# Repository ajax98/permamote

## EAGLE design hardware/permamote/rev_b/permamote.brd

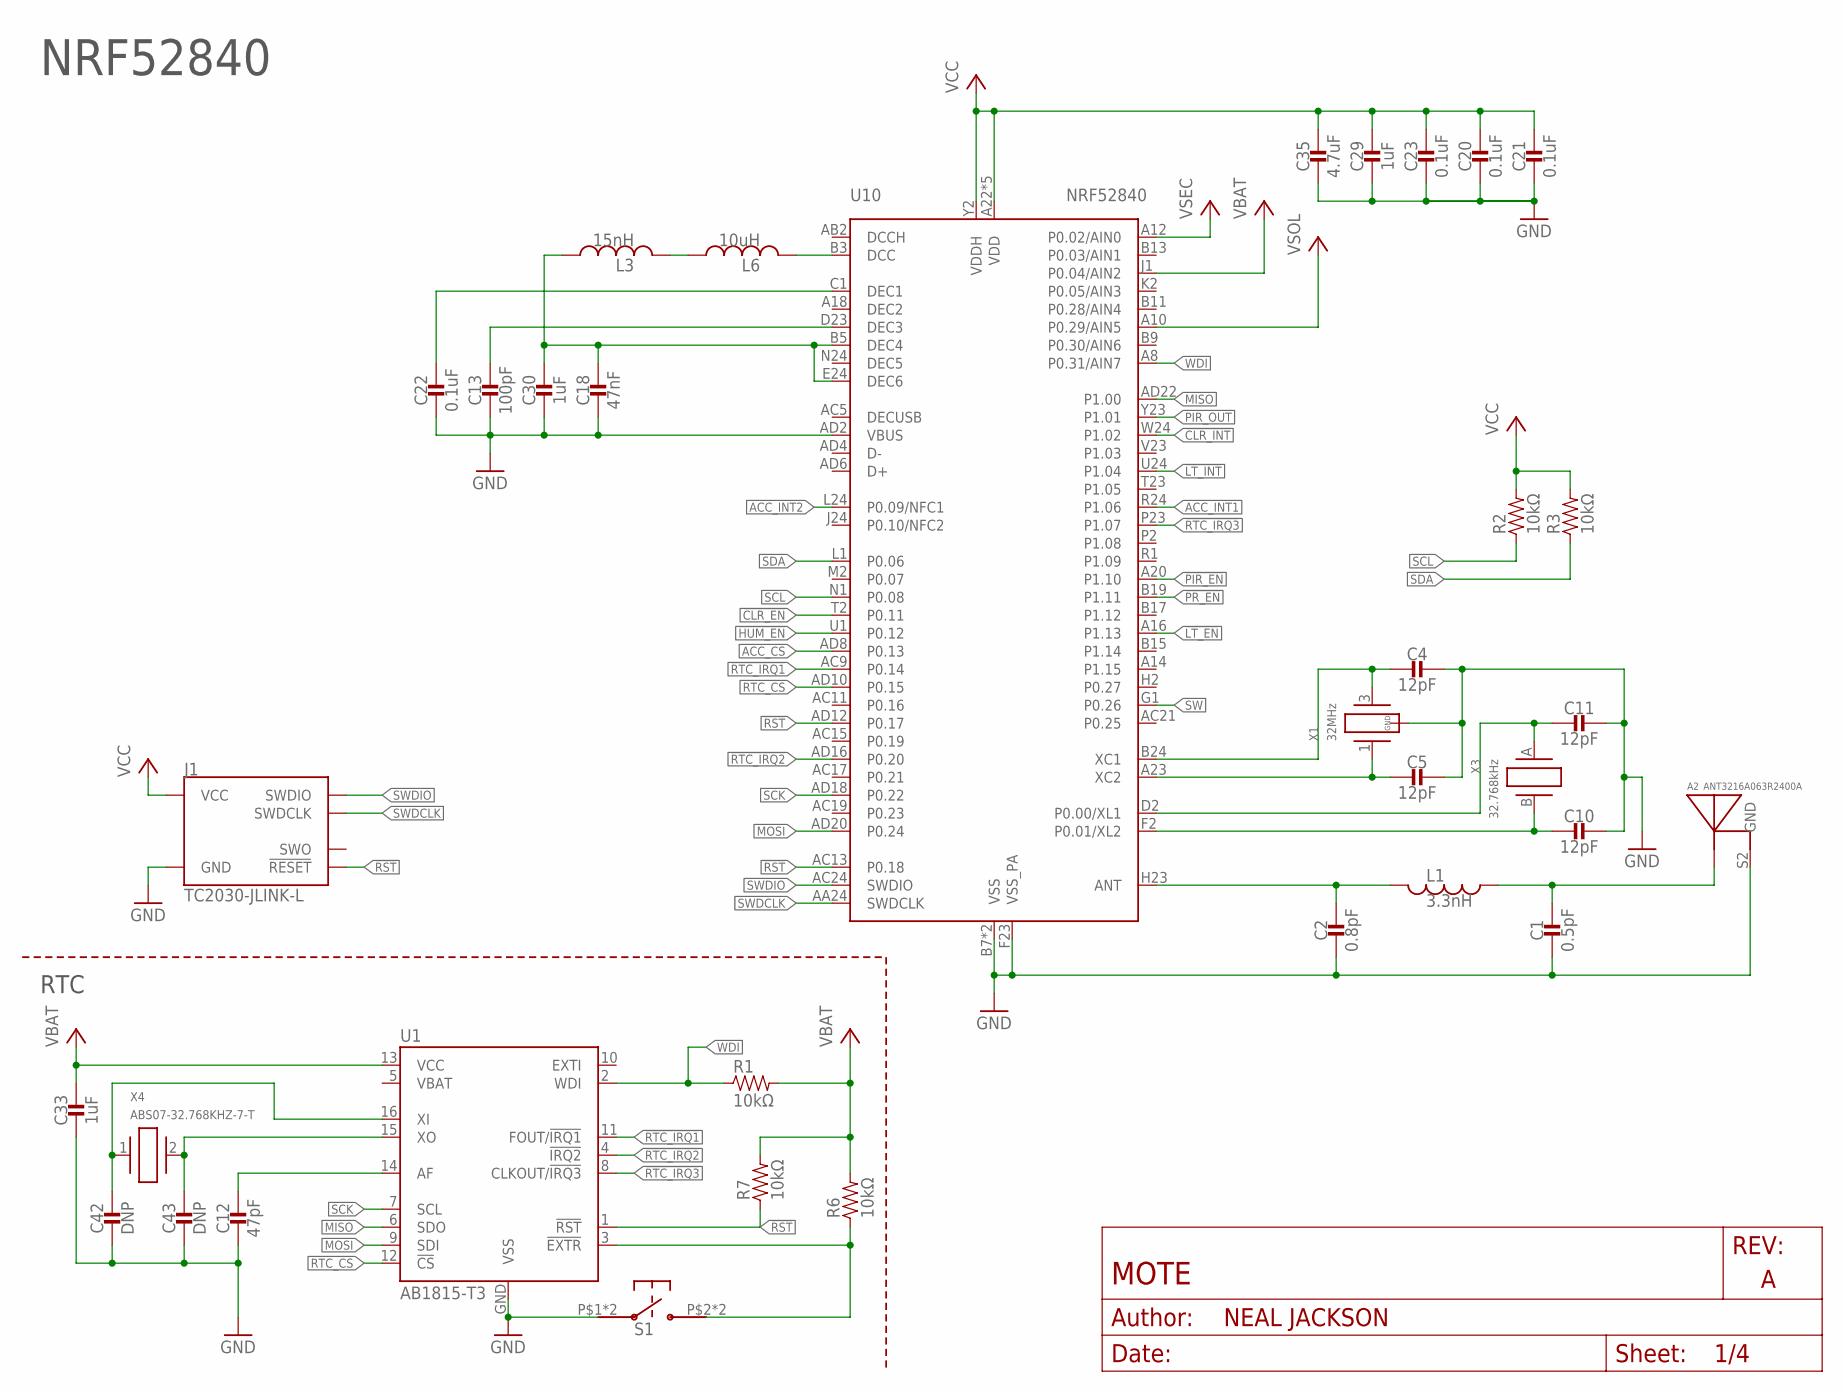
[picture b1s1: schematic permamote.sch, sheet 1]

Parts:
A2: ANT3216A063R2400A
C1: 0.5pF; 0402_CAP; DIGIKEY 490-6264-1-ND
C2: 0.8pF; 0402_CAP; DIGIKEY 490-6269-1-ND
C4, C5, C10, C11: 12pF; 0402_CAP; DIGIKEY 490-6197-1-ND
C12: 47pF; 0402_CAP; DIGIKEY 490-5942-1-ND
C13: 100pF; 0402_CAP; DIGIKEY 490-5922-1-ND
C18: 47nF; 0402_CAP; DIGIKEY 445-1264-1-ND
C20, C21, C22, C23: 0.1uF; 0402_CAP; DIGIKEY 490-6328-1-ND
C29, C30, C33: 1uF; 0402_CAP; DIGIKEY 490-7195-1-ND
C35: 4.7uF; 0402_CAP; DIGIKEY 445-5947-1-ND
C42, C43: DNP; 0402_CAP
J1: TC2030-JLINK-L; TC2030-IDC
L1: 3.3nH; 0402_CAP; DIGIKEY 535-10426-1-ND
L3: 15nH; 0402_CAP; DIGIKEY 587-1521-1-ND
L6: 10uH; 0603_CAP; DIGIKEY 490-4025-1-ND
R1, R2, R3, R6, R7: 10kΩ; 0402_RES; DIGIKEY 311-10KJRCT-ND
S1: EVQP2
U1: AB1815-T3; QFN-16-3MM
U10: NRF52840; AQFN73
X1: 32MHz; TXC-7V
X3: 32.768kHz; ABS05
X4: ABS07-32.768KHZ-7-T; 2-SMD

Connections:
!CLR_EN: U10.T2 (P0.11); also elsewhere on the board
!CLR_INT: U10.W24 (P1.02); also elsewhere on the board
!HUM_EN: U10.U1 (P0.12); also elsewhere on the board
!LT_EN: U10.A16 (P1.13); also elsewhere on the board
!LT_INT: U10.U24 (P1.04); also elsewhere on the board
!PIR_EN: U10.A20 (P1.10); also elsewhere on the board
!PR_EN: U10.B19 (P1.11); also elsewhere on the board
!RST: J1.3 (!RESET), R7.1, U1.1 (!RST), U10.AC13 (P0.18), U10.AD12 (P0.17); also elsewhere on the board
!RTC_EXTR: R6.1, S1.P$2, S1.P$4, U1.3 (!EXTR)
!RTC_IRQ1: U1.11 (FOUT/!IRQ1), U10.AC9 (P0.14); also elsewhere on the board
!RTC_IRQ2: U1.4 (!IRQ2), U10.AD16 (P0.20); also elsewhere on the board
!RTC_IRQ3: U1.8 (CLKOUT/!IRQ3), U10.P23 (P1.07); also elsewhere on the board
ACC_CS: U10.AD8 (P0.13); also elsewhere on the board
ACC_INT1: U10.R24 (P1.06); also elsewhere on the board
ACC_INT2: U10.L24 (P0.09/NFC1); also elsewhere on the board
GND: A2.S2 (GND), C1.2, C2.2, C4.1, C5.1, C10.1, C11.1, C12.2, C13.2, C18.2, C20.2, C21.2, C22.2, C23.2, C29.2, C30.2, C33.2, C35.2, C42.2, C43.2, J1.5 (GND), S1.P$1, S1.P$3, U1.GND (VSS), U10.AD2 (VBUS), U10.B7 (VSS), U10.F23 (VSS_PA), U10.GND (VSS), X1.2 (GND), X1.4 (GND); also elsewhere on the board
MISO: U1.6 (SDO), U10.AD22 (P1.00); also elsewhere on the board
MOSI: U1.9 (SDI), U10.AD20 (P0.24); also elsewhere on the board
unnamed: C22.1, U10.C1 (DEC1)
unnamed: C18.1, C30.1, L3.1, U10.B5 (DEC4), U10.E24 (DEC6)
unnamed: C13.1, U10.D23 (DEC3)
unnamed: C2.1, L1.2, U10.H23 (ANT)
unnamed: A2.S1 (ANTENNA), C1.1, L1.1
unnamed: C4.2, U10.B24 (XC1), X1.3 (2)
unnamed: C5.2, U10.A23 (XC2), X1.1
unnamed: C12.1, U1.14 (AF)
unnamed: C42.1, U1.16 (XI), X4.1
unnamed: C43.1, U1.15 (XO), X4.2
unnamed: L6.2, U10.B3 (DCC)
unnamed: L3.2, L6.1
PIR_OUT: U10.Y23 (P1.01); also elsewhere on the board
RTC_CS: U1.12 (!CS), U10.AD10 (P0.15); also elsewhere on the board
SCK: U1.7 (SCL), U10.AD18 (P0.22); also elsewhere on the board
SCL: R2.1, U10.N1 (P0.08); also elsewhere on the board
SDA: R3.1, U10.L1 (P0.06); also elsewhere on the board
SW: U10.G1 (P0.26); also elsewhere on the board
SWDCLK: J1.4 (SWDCLK), U10.AA24 (SWDCLK)
SWDIO: J1.2 (SWDIO), U10.AC24 (SWDIO)
VBAT: C33.1, R1.2, R6.2, R7.2, U1.13 (VCC), U10.J1 (P0.04/AIN2); also elsewhere on the board
VCC: C20.1, C21.1, C23.1, C29.1, C35.1, J1.1 (VCC), R2.2, R3.2, U10.A22 (VDD), U10.AD14 (VDD), U10.AD23 (VDD), U10.B1 (VDD), U10.W1 (VDD), U10.Y2 (VDDH); also elsewhere on the board
VSEC: U10.A12 (P0.02/AIN0); also elsewhere on the board
VSOL: U10.A10 (P0.29/AIN5); also elsewhere on the board
WDI: R1.1, U1.2 (WDI), U10.A8 (P0.31/AIN7); also elsewhere on the board
XL1: C11.2, U10.D2 (P0.00/XL1), X3.A (1)
XL2: C10.2, U10.F2 (P0.01/XL2), X3.B (2)

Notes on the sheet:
NRF52840
RTC

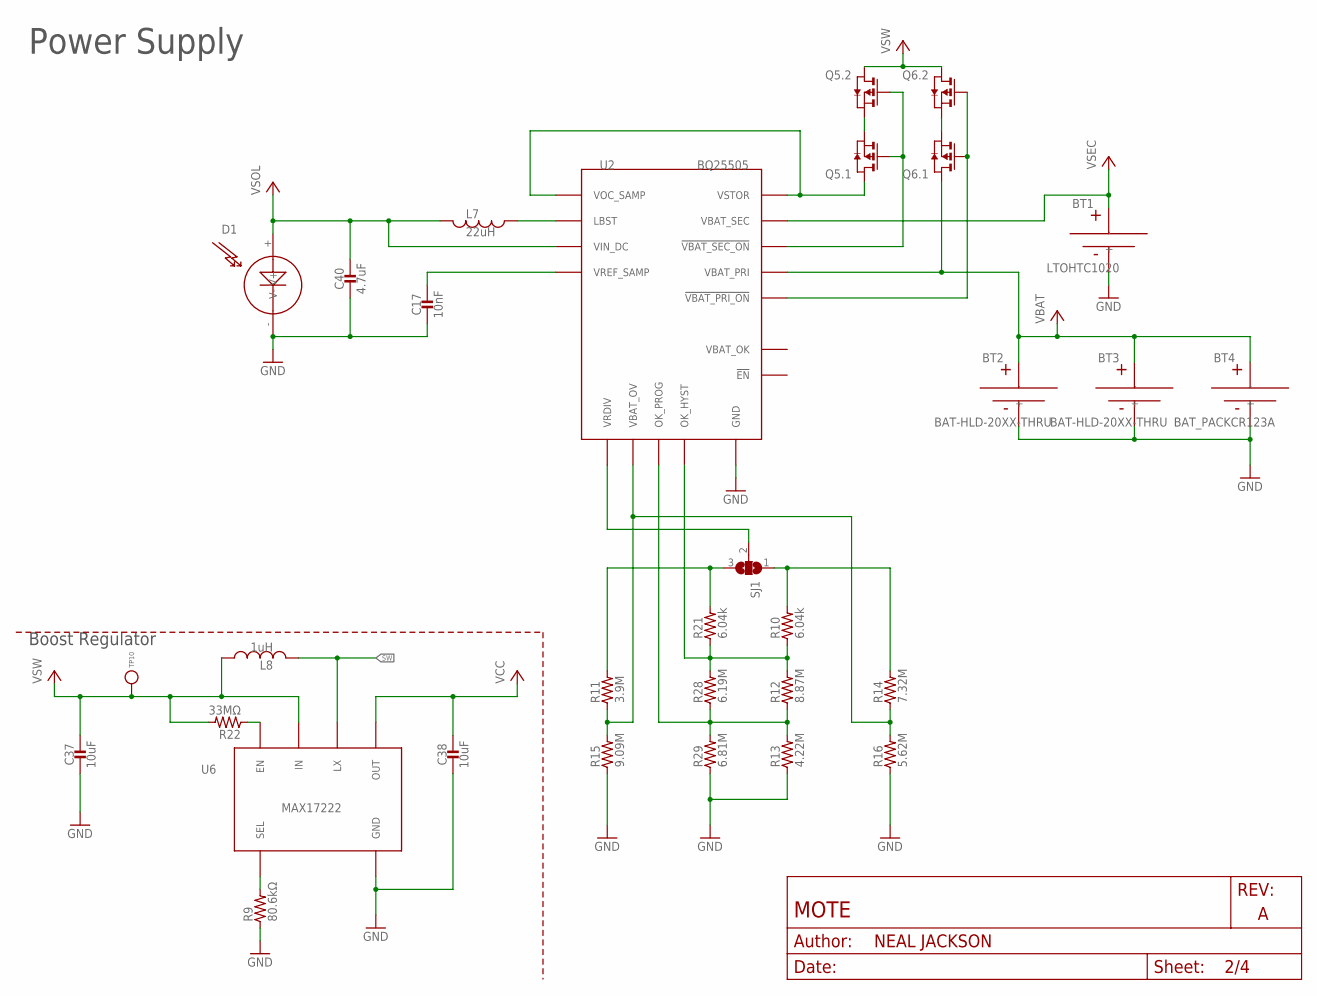
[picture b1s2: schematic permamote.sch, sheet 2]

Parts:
BT1: LTOHTC1020; 1020
BT2, BT3: BAT-HLD-20XX-THRU
BT4: BAT_PACKCR123A; BH123A
C17: 10nF; 0603_CAP; DIGIKEY 490-4516-1-ND
C37, C38: 10uF; 0603_CAP; DIGIKEY 490-3896-1-ND
C40: 4.7uF; 0603_CAP; DIGIKEY 490-3896-1-ND
D1: SOLARCELL; SOLAR_HOLES
L7: 22uH; 74437324220; DIGIKEY 732-3340-1-ND
L8: 1uH; IHL-1212BZ-11; MPN IHLP1212BZER1R0M11; DIGIKEY 541-1319-1-ND
Q5, Q6: PMDXB950UPEL; XDFN-6
R9: 80.6kΩ; 0603-RES; DIGIKEY 311-80.6KHRCT-ND
R10, R21: 6.04k; 0402_RES; DIGIKEY YAG3306CT-ND
R11: 3.9M; 0402_RES; DIGIKEY YAG3306CT-ND
R12: 8.87M; 0402_RES; DIGIKEY YAG3306CT-ND
R13: 4.22M; 0402_RES; DIGIKEY YAG3306CT-ND
R14: 7.32M; 0402_RES; DIGIKEY YAG3306CT-ND
R15: 9.09M; 0402_RES; DIGIKEY YAG3306CT-ND
R16: 5.62M; 0402_RES; DIGIKEY YAG3306CT-ND
R22: 33MΩ; 0603-RES; DIGIKEY HMC0603JT33M0CT-ND
R28: 6.19M; 0402_RES; DIGIKEY YAG3306CT-ND
R29: 6.81M; 0402_RES; DIGIKEY YAG3306CT-ND
SJ1: SJ2W; SJ_2
TP10: TEST_POINT_0.040IN; TESTPOINT_0.040IN
U2: BQ25505; S-PVQFN-N20-RGR
U6: MAX17222; UDFN-6-MAXIM

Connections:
GND: BT1.-, BT2.GND (-), BT3.GND (-), BT4.-, C17.2, C37.2, C38.2, C40.2, D1.- (V-), R9.1, R13.1, R15.1, R16.1, R29.1, U2.1 (GND), U2.6 (GND), U2.15 (GND), U2.16 (GND), U2.17 (GND), U2.PAD (GND), U6.3 (GND); also elsewhere on the board
unnamed: R11.2, R21.2, SJ1.3
unnamed: R9.2, U6.4 (SEL)
unnamed: R22.1, U6.6 (EN)
unnamed: R10.2, R14.2, SJ1.1
unnamed: R11.1, R14.1, R15.2, R16.2, U2.7 (VBAT_OV)
unnamed: C17.1, U2.4 (VREF_SAMP)
unnamed: SJ1.2, U2.8 (VRDIV)
unnamed: L7.P$1 (1), U2.20 (LBST)
unnamed: Q5.1 (S), Q5.4 (S)
unnamed: Q5.2 (G), Q5.5 (G), U2.9 (!VBAT_SEC_ON)
unnamed: Q5.6 (D), U2.3 (VOC_SAMP), U2.19 (VSTOR)
unnamed: Q6.1 (S), Q6.4 (S)
unnamed: Q6.2 (G), Q6.5 (G), U2.10 (!VBAT_PRI_ON)
unnamed: R12.1, R13.2, R28.1, R29.2, U2.12 (OK_PROG)
unnamed: R10.1, R12.2, R21.1, R28.2, U2.11 (OK_HYST)
SW: L8.P$2 (2), U6.2 (LX); also elsewhere on the board
VBAT: BT2.+1 (+), BT2.+2 (+), BT2.+3 (+), BT2.+4 (+), BT3.+1 (+), BT3.+2 (+), BT3.+3 (+), BT3.+4 (+), BT4.+, Q6.6 (D), U2.14 (VBAT_PRI); also elsewhere on the board
VCC: C38.1, U6.1 (OUT); also elsewhere on the board
VSEC: BT1.+, U2.18 (VBAT_SEC); also elsewhere on the board
VSOL: C40.1, D1.+ (V+), L7.P$2 (2), U2.2 (VIN_DC); also elsewhere on the board
VSW: C37.1, L8.P$1 (1), Q5.3 (D), Q6.3 (D), R22.2, TP10.TESTPOINT, U6.5 (IN)

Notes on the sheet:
Power Supply
Boost Regulator

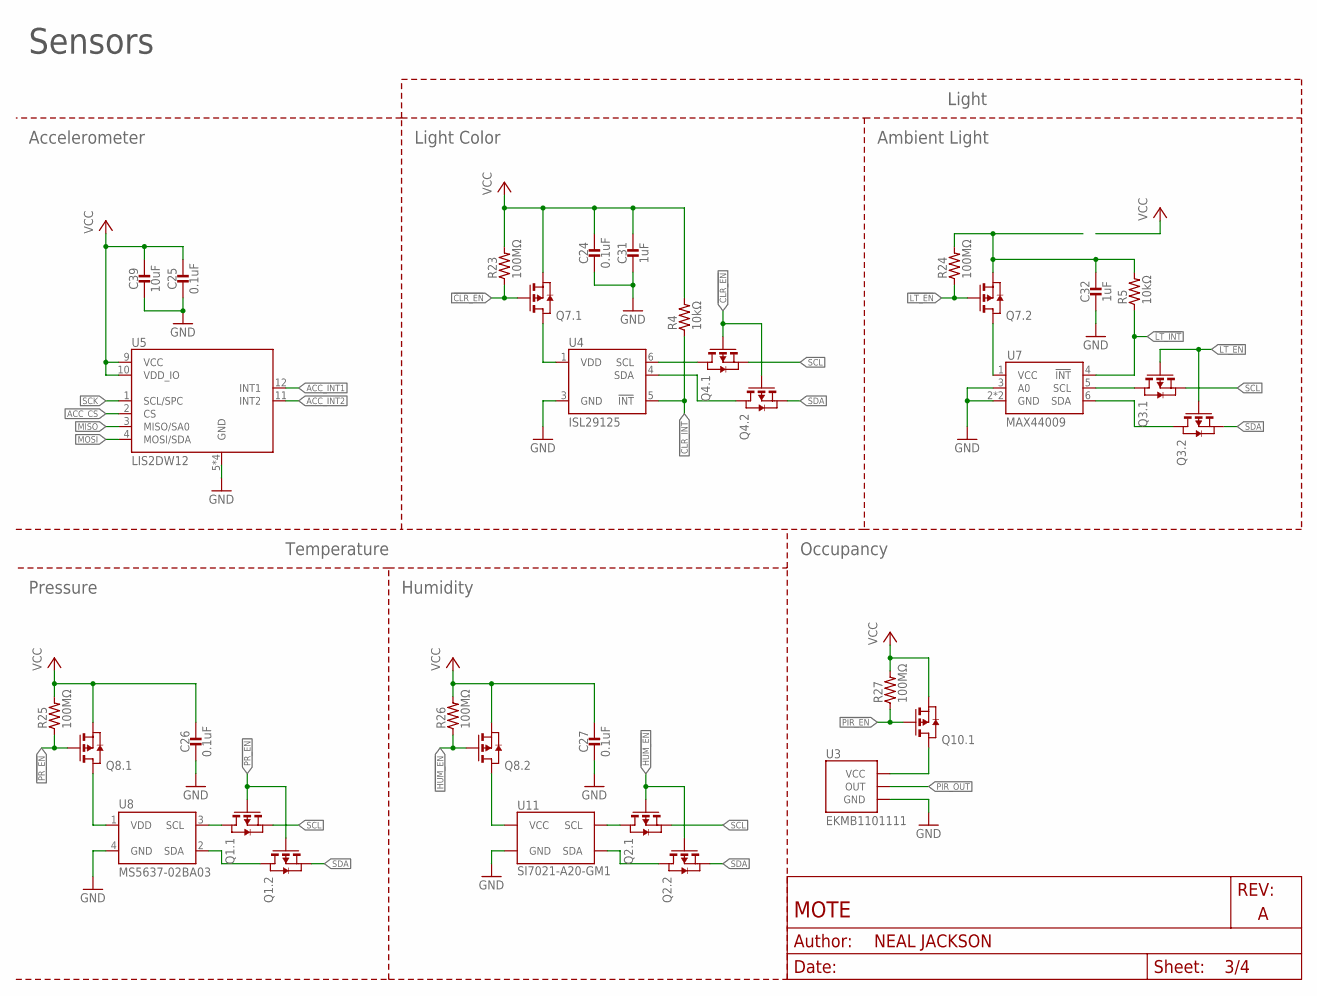
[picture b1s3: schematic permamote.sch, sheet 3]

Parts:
C24, C25, C26, C27: 0.1uF; 0402_CAP; DIGIKEY 490-6328-1-ND
C31, C32: 1uF; 0402_CAP; DIGIKEY 490-7195-1-ND
C39: 10uF; 0603_CAP; DIGIKEY 490-3896-1-ND
Q1, Q2, Q3, Q4, Q7, Q8, Q10: PMDXB950UPEL; XDFN-6
R4, R5: 10kΩ; 0402_RES; DIGIKEY 311-10KJRCT-ND
R23, R24, R25, R26, R27: 100MΩ; 0402_RES; DIGIKEY 541-100MAHCT-ND
U3: EKMB1101111; AMN2
U4: ISL29125; ODFN-6-1.5MMX1.6MM
U5: LIS2DW12; LGA-12
U7: MAX44009; UDFN-6-EXPOSED
U8: MS5637-02BA03; 4-SMD
U11: SI7021-A20-GM1; DFN-6/3MM

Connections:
!CLR_EN: Q4.2 (G), Q4.5 (G), Q7.2 (G), R23.1; also elsewhere on the board
!CLR_INT: R4.1, U4.5 (!INT); also elsewhere on the board
!HUM_EN: Q2.2 (G), Q2.5 (G), Q8.5 (G), R26.1; also elsewhere on the board
!LT_EN: Q3.2 (G), Q3.5 (G), Q7.5 (G), R24.1; also elsewhere on the board
!LT_INT: R5.1, U7.4 (!INT); also elsewhere on the board
!PIR_EN: Q10.2 (G), R27.1; also elsewhere on the board
!PR_EN: Q1.2 (G), Q1.5 (G), Q8.2 (G), R25.1; also elsewhere on the board
ACC_CS: U5.2 (CS); also elsewhere on the board
ACC_INT1: U5.12 (INT1); also elsewhere on the board
ACC_INT2: U5.11 (INT2); also elsewhere on the board
GND: C24.2, C25.2, C26.2, C27.2, C31.2, C32.2, C39.2, U3.GND, U4.3 (GND), U5.5 (GND), U5.6 (GND), U5.7 (GND), U5.8 (GND), U7.2 (GND), U7.3 (A0), U7.EP (GND), U8.4 (GND), U11.2 (GND); also elsewhere on the board
MISO: U5.3 (MISO/SA0); also elsewhere on the board
MOSI: U5.4 (MOSI/SDA); also elsewhere on the board
unnamed: Q7.3 (D), U7.1 (VCC)
unnamed: Q8.6 (D), U8.1 (VDD)
unnamed: Q8.3 (D), U11.5 (VCC)
unnamed: Q10.6 (D), U3.VCC
unnamed: Q7.6 (D), U4.1 (VDD)
unnamed: Q1.6 (D), U8.3 (SCL)
unnamed: C32.1, Q7.4 (S), R5.2, R24.2
unnamed: Q1.3 (D), U8.2 (SDA)
unnamed: Q2.3 (D), U11.1 (SDA)
unnamed: Q2.6 (D), U11.6 (SCL)
unnamed: Q3.3 (D), U7.6 (SDA)
unnamed: Q3.6 (D), U7.5 (SCL)
unnamed: Q4.3 (D), U4.4 (SDA)
unnamed: Q4.6 (D), U4.6 (SCL)
PIR_OUT: U3.OUT; also elsewhere on the board
SCK: U5.1 (SCL/SPC); also elsewhere on the board
SCL: Q1.1 (S), Q2.1 (S), Q3.1 (S), Q4.1 (S); also elsewhere on the board
SDA: Q1.4 (S), Q2.4 (S), Q3.4 (S), Q4.4 (S); also elsewhere on the board
VCC: C24.1, C25.1, C26.1, C27.1, C31.1, C39.1, Q7.1 (S), Q8.1 (S), Q8.4 (S), Q10.1 (S), R4.2, R23.2, R25.2, R26.2, R27.2, U5.9 (VCC), U5.10 (VDD_IO); also elsewhere on the board

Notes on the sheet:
Sensors
Accelerometer
Temperature
Humidity
Pressure
Ambient Light
Light Color
Light
Occupancy

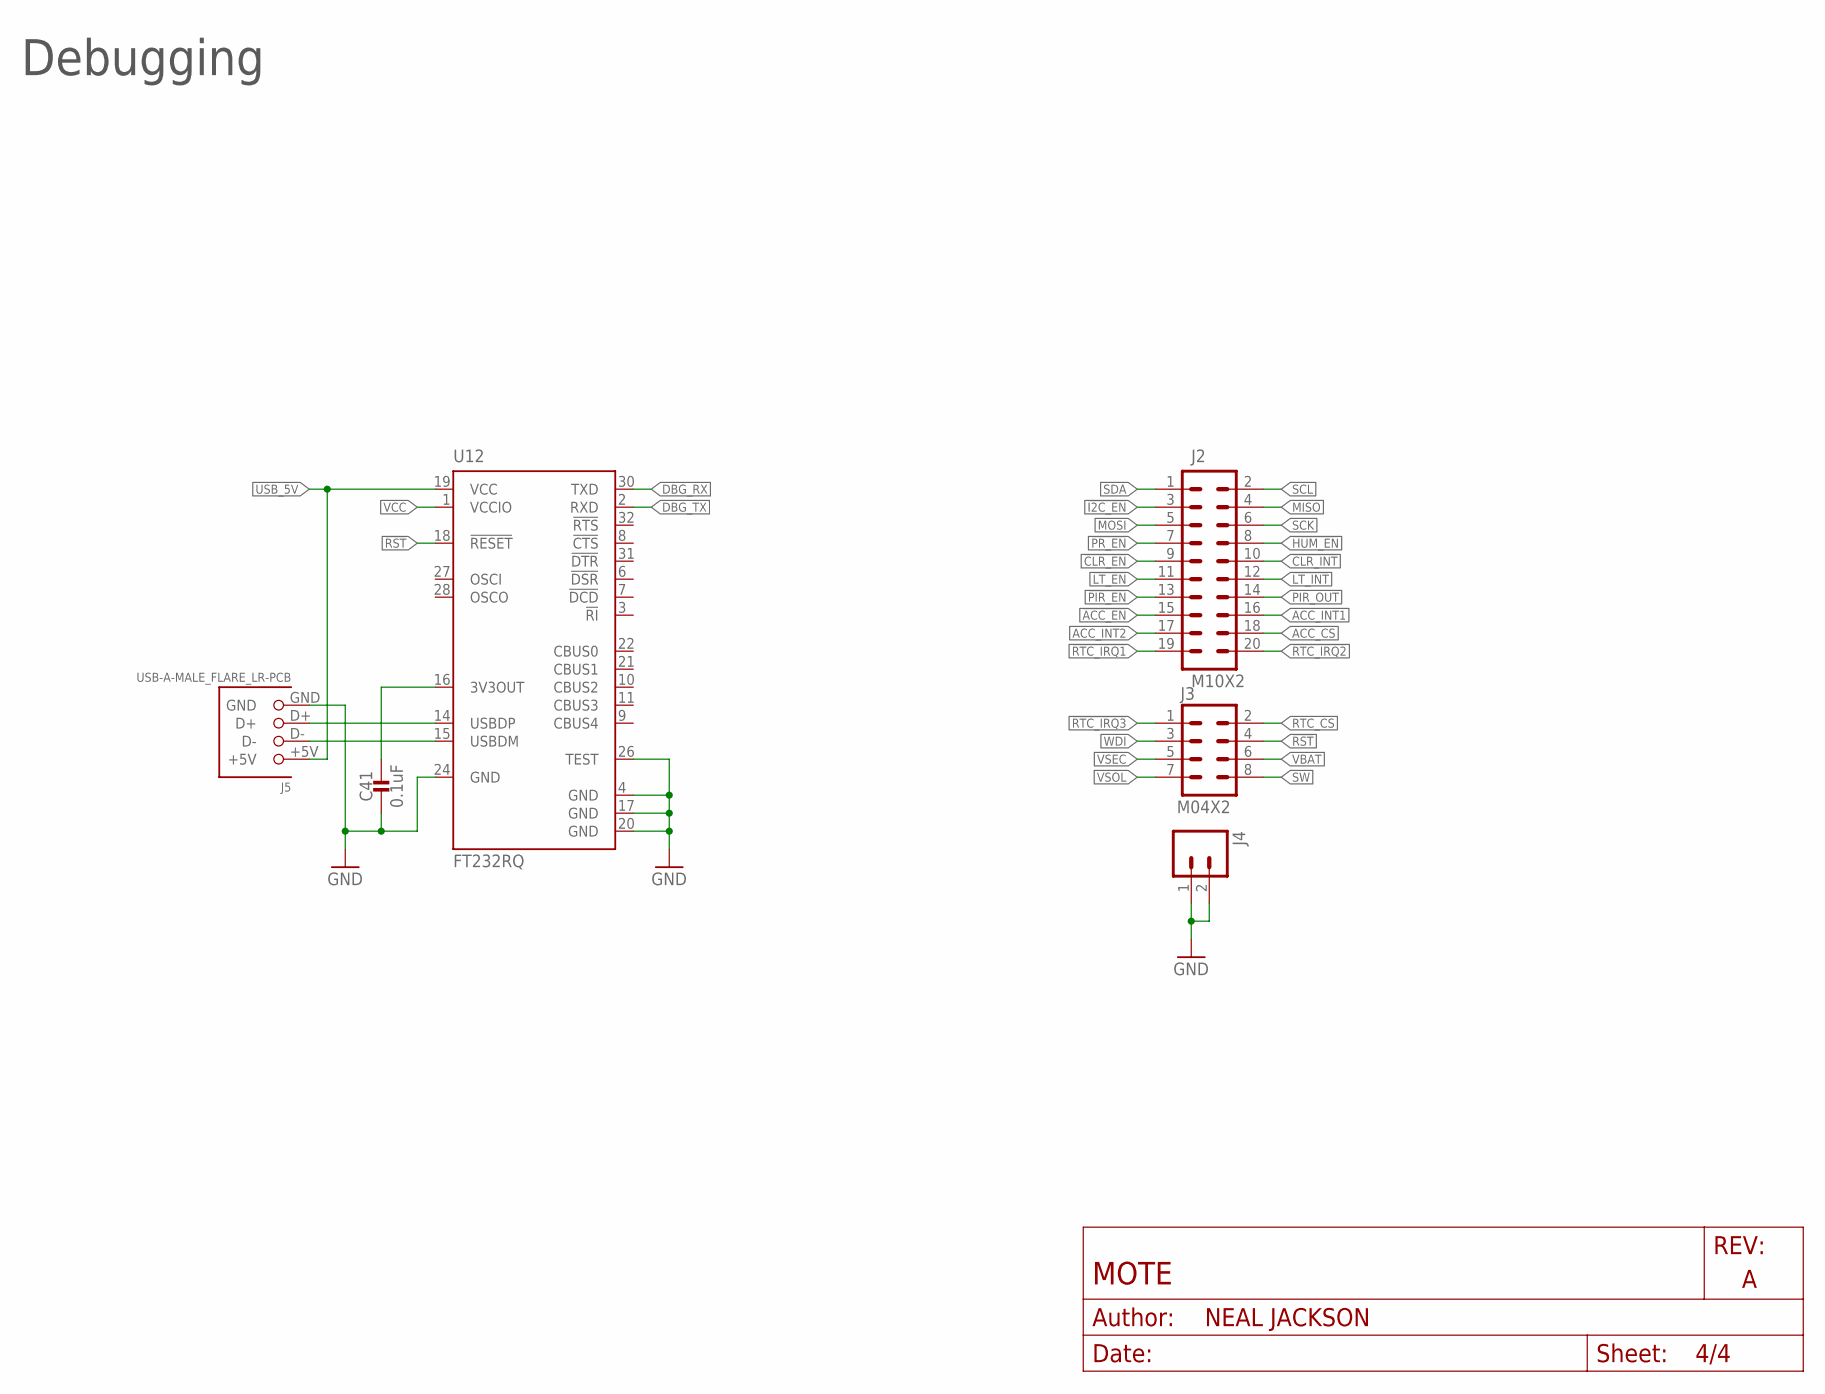
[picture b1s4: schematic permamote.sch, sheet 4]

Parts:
C41: 0.1uF; 0402_CAP; DIGIKEY 490-6328-1-ND
J2: M10X2; 2X10
J3: M04X2; 2X4
J4: M02PTH; 1X02
J5: USB-A-MALE_FLARE_LR-PCB; USB-A-MALE_FLARE_LR
U12: FT232RQ; QFN32

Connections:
!ACC_EN: J2.15
!CLR_EN: J2.9; also elsewhere on the board
!CLR_INT: J2.10; also elsewhere on the board
!HUM_EN: J2.8; also elsewhere on the board
!I2C_EN: J2.3
!LT_EN: J2.11; also elsewhere on the board
!LT_INT: J2.12; also elsewhere on the board
!PIR_EN: J2.13; also elsewhere on the board
!PR_EN: J2.7; also elsewhere on the board
!RST: J3.4, U12.18 (!RESET); also elsewhere on the board
!RTC_IRQ1: J2.19; also elsewhere on the board
!RTC_IRQ2: J2.20; also elsewhere on the board
!RTC_IRQ3: J3.1; also elsewhere on the board
ACC_CS: J2.18; also elsewhere on the board
ACC_INT1: J2.16; also elsewhere on the board
ACC_INT2: J2.17; also elsewhere on the board
DBG_RX: U12.30 (TXD)
DBG_TX: U12.2 (RXD)
GND: C41.2, J4.1, J4.2, J5.GND, U12.4 (GND), U12.17 (GND), U12.20 (GND), U12.24 (GND), U12.26 (TEST); also elsewhere on the board
MISO: J2.4; also elsewhere on the board
MOSI: J2.5; also elsewhere on the board
unnamed: C41.1, U12.16 (3V3OUT)
PIR_OUT: J2.14; also elsewhere on the board
RTC_CS: J3.2; also elsewhere on the board
SCK: J2.6; also elsewhere on the board
SCL: J2.2; also elsewhere on the board
SDA: J2.1; also elsewhere on the board
SW: J3.8; also elsewhere on the board
USB_5V: J5.+5V, U12.19 (VCC)
USB_D+: J5.D+, U12.14 (USBDP)
USB_D-: J5.D-, U12.15 (USBDM)
VBAT: J3.6; also elsewhere on the board
VCC: U12.1 (VCCIO); also elsewhere on the board
VSEC: J3.5; also elsewhere on the board
VSOL: J3.7; also elsewhere on the board
WDI: J3.3; also elsewhere on the board

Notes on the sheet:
Debugging

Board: 4 copper layers, 98 parts (0 on the bottom side), 79 nets, no tracks yet.

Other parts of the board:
U$1: UCB_CAL_200MIL

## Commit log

2017-11-19 WIP rev_b
2017-11-19 fix check for NRF52840
2017-11-19 add acc app
2017-11-19 make some apps nrf52 compatible

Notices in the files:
parts and their libraries:
SparkFun-Connectors: Licensing: CC v3.0 Share-Alike You are welcome to use this library for commercial purposes.
